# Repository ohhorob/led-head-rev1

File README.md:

# LED Head Unit · Rev 1

## Modular redesign — 2026-11-20

The new modular design lives in separate projects in this same repository:

- [Pico carrier](pico-carrier/README.md): populated control/monitoring schematic and unrouted PCB draft.
- [Power manager](power-manager/README.md): empty KiCad starter project.
- [String daughtercard](string-daughterboard/README.md): existing routed card, preserved.
- [Shared interfaces](shared/README.md): connector pinout, mechanical contract and verification tool.

Open the relevant `.kicad_pro`, rather than opening its PCB on its own. The combined board described below is retained as the earlier design; its control/monitoring circuits have started migrating into the carrier; the power manager remains a starter project.

Open `led-head-rev1.kicad_pro` in KiCad 10. The project contains the schematic, PCB and draft SMT assembly data. The nominal outline is 100 × 73 mm with a notch under the socketed Pico 2 W antenna. The enclosure must leave the antenna end clear of wiring, battery and metal hardware. Check USB and SWD reach, socket height and harness opening clearance against the physical parts.

## Board and harness

| Ref | Connection |
| --- | --- |
| J1 | Shared board-mounted XT60PW-M. Pin 1 is ground and pin 2 is positive. Connect a regulated 5 V supply, a fused 3S LiPo, or a fused 12 V LiFePO₄ camper circuit with BMS protection. Keep the 5 A fuse in the battery harness and size the 5 V source-side fuse for its wiring and load. |
| J3 | High-current panel toggle connections. Board pin 1 (EXT_5V) to S333 lug 3, pin 2 (LED_5V) to lug 2, pin 3 (BUCK_5V) to lug 1. |
| J5 | Toggle auxiliary pole. Board pin 1 to S333 lug 6, pin 2 to lug 5, pin 3 to lug 4. |
| MOD1 | Plug-in Pololu D36V50F5 (4091). Solder two 1×6 female sockets to the carrier and two matching male strips to the module. The pin pitch is 2.54 mm. Use every VIN, VOUT and GND pad. See the mounting details below. |
| J10/J11 | Female 1×20 sockets, on the standard 17.78 mm row spacing. J10 pin 1 is Pico pin 1. J11 pin 1 is Pico pin 21. |
| J12 | NeoTrellis JST-PH. Pins 1–4 on this board are GND, 3.3 V, SDA, SCL. Map the harness wire by wire to the actual keypad; a generic straight-through JST-PH cable is provisional. Check the keypad power budget. |
| J21–J23 | Right-angle JST-XH S3B-XH-A(LF)(SN) string outputs. Pin 1 = GND, pin 2 = DATA, pin 3 = fused and sensed +5 V. Use an XHP-3 housing with SXH-001T-P0.6 contacts and 22 AWG leads to the matching string-side JST-SM connector. Verify the string pin order before crimping. |
| J16 | UART0 for Adafruit 4331. Pin 1 (square, black cable wire) = GND, pin 4 = Pico RX (GP1), pin 5 = Pico TX (GP0). Pins 2, 3 and 6 are unconnected. |
| J17 | SPI0, six-pin JST-PH. Pins 1–6 are GND, switched LED_5V, MISO/GP16, CSn/GP17, SCK/GP18, MOSI/GP19. SPI signals use 3.3 V logic. |
| TP2–TP5 | Standard 2.54 mm 1×2 headers for Logic Pro probes. Pin 1 (square) is signal and pin 2 is ground. TP2 = INA3221 bus SDA, TP3 = INA3221 bus SCL, TP4 = Trellis bus SDA, TP5 = Trellis bus SCL. |

The NKK S333 pole 1 selects the Pololu output or the protected 5 V bypass with OFF between. Label the switch BAT / OFF / 5 V. The second pole grounds buck EN in 5 V mode and grounds the source ID input on the battery setting. Verify switch terminal numbering and lever positions with continuity before marking the enclosure. The switch mounts to the enclosure and connects using a harness. Keep the switch power loop short, use suitably rated wire and strain relief, and ventilate the carrier-mounted Pololu module. The unit and all outputs share DC ground.

The 13.7 kΩ EN pull-down works with the Pololu's nominal internal 100 kΩ pull-up. Nominal loaded cutoff is 9.96 V and restart is 11.20 V from the 1.2/1.35 V EN thresholds. Confirm both with the actual module. The firmware should blank the LEDs before the hardware cutoff. A pack-level threshold cannot identify an imbalanced cell. The camper source uses its own BMS/low-voltage protection. ADC reporting should show volts without inferring chemistry.

Pico GP4/GP5/GP6 remain LED lanes 1–3. GP8/GP9 are hardware I²C0 SDA/SCL for the INA3221, with R7/R8 pull-ups and TP2/TP3 probe headers. NeoTrellis is on hardware I²C1: physical pin 19 (GP14) is SDA and physical pin 20 (GP15) is SCL. The carrier adds no pull-ups to this bus. Use the pull-ups on the connected keypad. GP7 reads the active-low battery-select signal, GP10 reads buck PG, and GP26 is battery ADC. Firmware must add current monitoring, keypad, source sensing and current limiting on top of the existing output paths. The nominal budgets are 1.8 A per string and 4.5 A aggregate LED load on battery. The board power distribution target is 6 A of LEDs plus controller and keypad overhead on external 5 V.

Three TXU0101 buffers replace the originally planned AHCT125. Each output-side supply is taken after its own fuse and shunt, so the data driver isolates when that rail or Pico 3.3 V is absent. Each shunt is 50 mΩ, dropping 100 mV and dissipating 0.20 W at 2 A. Check fuse trip coordination, inrush through the switch and actual connector voltage at full load. Fuse removal and harness changes are performed with power off.

## Four layers, 1 oz copper on both outside layers

Fabrication intent is 1.6 mm FR-4, four layers, **1 oz finished outer copper on both layers**. The 4.8 mm switched trunk, 4.2 mm bypass trunk downstream of the eFuse fan-out, 4.0 mm buck feed, and 1.9 mm per-string top routes are present as copper. String rail fan-outs use 2.3 mm copper and four 0.4 mm drilled vias per string. Positive power routing stays on the outer layers. The dedicated In1 ground plane complements the backside ground pour, with solid connections to high-current through-hole pads. In2 provides room for signal crossovers. Specify 1 oz for the In1 return plane if the fabricator offers it, and verify the chosen stackup on the quote.

IPC-2221 external-trace screening at nominal 35 µm copper gives approximately 3.97 mm for 6.5 A, 2.77 mm for 5 A and 0.78 mm for 2 A at 10 °C rise. Treat these as screening values for straight, uniform traces. Connector annuli, fuse pads, shunt pads, via plating and the minimum width of the actual filled return paths need review as individual bottlenecks. Validate populated electrical and thermal performance with a current-limited bench supply, then at 6 A external and the intended battery load inside the enclosure.

## SMT quote

Request top-side SMT only. Load the supplied BOM and centroid files as quote drafts and review the pin-one and diode orientation on the vendor placement preview. The Pico sockets, screw terminals, XT60 and XH headers, NeoTrellis PH header and bulk electrolytic are through-hole and installed separately. Install the Pololu module and its two headers by hand. The panel switch and mating battery harness are off-board. If using JLCPCB, match the exact manufacturer parts to its catalog before placing the order. In particular, confirm sourcing for the TPS25970ARPWR, the three TXU0101DBVRs, the INA3221, 3 A fuse and shunts. Verify the RPW0010A land pattern, stencil openings, and pin 1 against the assembly preview. PCBWay can quote these by manufacturer part number. Release Gerbers and the placement files together from the same verified PCB revision.

## Review status

KiCad 10 electrical-rule and design-rule reports are included, including board/schematic parity. Both design-rule checks and a vendor placement preview are separate from an electrical prototype test. First articles should verify the physical socket orientation, harness polarity, NeoTrellis pin mapping, S333 auxiliary-contact operation, source-change inrush, 3S cutoff/restart, and voltage drop/temperature in the populated enclosure. Use correctly polarized XT60 leads. The eFuse bypass and input-side status electronics depend on correct polarity.

The firmware is unchanged in its original project. The preserved outputs can drive the existing strings. New sensing, keypad and current-budget behavior require firmware work before relying on the stated limits.

References: [IPC-2221 screening calculator](https://www.digikey.com/en/resources/conversion-calculators/conversion-calculator-pcb-trace-width), [Pico 2 W datasheet](https://datasheets.raspberrypi.com/picow/pico-2-w-datasheet.pdf), [Pololu D36V50F5](https://www.pololu.com/product/4091), [NKK S-series](https://www.nkk.com/pdf/toggle_S.pdf), [TI TXU0101](https://www.ti.com/product/TXU0101), [TI INA3221](https://www.ti.com/product/INA3221), [JLCPCB assembly files](https://jlcpcb.com/help/article/how-to-generate-the-bom-and-centroid-file-from-kicad), [PCBWay assembly files](https://www.pcbway.com/assembly-file-requirements.html).

This revision includes Gerbers and separate plated/non-plated drill files for quote review. The KiCad 10.0.7 checks on the archived revision returned zero ERC violations, zero DRC violations, zero unconnected items and zero schematic-parity issues. The SMT BOM and placement file contain 71 positions. The fabrication and placement files in this package supersede the earlier Rev 1 exports.

## VSYS update

F4 was removed. The switched LED_5V rail now feeds D1 directly via a 0.65 mm branch with a 0.40 mm drill through via. D1 remains in series for USB isolation. Its cathode reaches J11 pad 19 on 0.65 mm front copper. The LED string fuses F1–F3 are retained.

## Connector silkscreen

J12 NEOTRELLIS marks the rotated four-pin JST-PH on the left. The combined string outlets are marked STR 1–3. The D, + and − markings identify data, fused +5 V and ground. J5 identifies the switch logic harness. MOD1 identifies the direct-mount regulator. The shared XT60 input has + and − markings.

## Connector access

The shared J1 XT60 inlet exits the right edge. The three JST-XH string outlets exit the top edge and overhang it for plug access. The J1 mating face projects approximately 5.4 mm beyond the PCB edge. The installed KiCad library has no STEP model for XT60PW-M; use the footprint fabrication outline to review the projection. Verify enclosure openings and wire bend radius with the actual harnesses.

## Pololu mounting

MOD1 uses the Pololu STEP model and generic KiCad models for two 1×6 female sockets and two downward-facing male strips. The modeled stack puts the module PCB underside 11.04 mm above the carrier surface (8.50 mm socket height plus a 2.54 mm male-header spacer). Measure the fully seated hardware before sizing the nylon standoff. The three module mounting-hole centers are indicated on the KiCad Drawings layer for support design. H5 is a 2.2 mm non-plated M2 clearance hole centered at (76.159, 30.759) mm, aligned with the upper-left MOD1 hole in PCB top view.

Viewed from the carrier top with the connector row toward the lower edge of the module, pads 1–6 are on the outer row and pads 7–12 on the inner row. Both rows run left to right.

| Row | Left to right |
| --- | --- |
| Outer (1–6) | VRP, EN, VOUT, VOUT, GND, VIN |
| Inner (7–12) | VRP, PG, VOUT, VOUT, GND, VIN |

Compare the physical module labels to the carrier pin mapping before soldering. Keep airflow around the converter and the existing battery-mode power budget pending a loaded thermal test.

## Shared inlet and status LEDs

| Toggle | Power path | Status |
| --- | --- | --- |
| BAT | J1 through the Pololu | POWER follows the switched rail. FAULT lights if Pololu PG is low after the BAT delay. |
| OFF | Neither throw connects to the switched rail | POWER goes dark as the rail discharges. FAULT is gated off. |
| 5 V | J1 through the TPS25970A eFuse | POWER follows the switched rail. FAULT is gated off. If J1 sees battery voltage, the bypass is blocked. |

The eFuse nominal rising thresholds are 4.33 V for enable and 5.38 V for overvoltage cutoff. With a 768 Ω ILIM resistor the nominal current-limit setpoint is 7.48 A, distinct from the device's 7 A continuous rating. The 6.8 nF DVDT capacitor slows startup when the eFuse enables. Switching to an already energized bypass can still cause inrush into C2. The output uses six plated vias into its 4.2 mm trunk. Inspect the short fan-outs from the RPW power contacts during the loaded test. Validate voltage drop and temperature at the 6 A LED load plus controller overhead before fabrication sign-off.

The red LED uses an input-side 3.3 V LDO independent of Pico power. D2 and D3 isolate the Pico inputs from that supply when the Pico is off. The BAT delay uses a 100 kΩ and 4.7 µF network with a Schmitt input, so timing depends on component and input-threshold tolerances. A depleted battery may be indicated as a fault while input power is sufficient to light the LED. If J1 is unplugged, the indicator has no supply.

With a current-limited bench source and the strings disconnected, test each switch mode, verify the overvoltage cutoff with battery-level input in 5 V mode, and scope the switched rail during hot-plug and source changes. Verify the fault LED with PG low while the Pico supply is absent. Follow with the loaded thermal and enclosure tests.

[TI TPS2597 datasheet](https://www.ti.com/lit/ds/symlink/tps2597.pdf) · [TI SN74LVC1G57 datasheet](https://www.ti.com/lit/ds/symlink/sn74lvc1g57.pdf)

## Pre-fabrication board review

Use Panasonic EEU-FR1C102 for C2 (1,000 µF, 16 V, 10 mm body and 5 mm lead pitch). The suffixed EEU-FR1C102L uses 3.5 mm lead pitch. The U4 INA3221 and R11–R13 shunt land patterns are in the project footprint library and follow the TI and Vishay reference dimensions. The SMT placement file was exported from the manually routed board. The native KiCad PCB is the source for subsequent edits.

The current layout passed KiCad ERC, DRC and schematic parity. The documented design-rule exclusions remain in the reports. Review the silkscreen and regenerate all final fabrication outputs from the resulting PCB. Verify assembly sourcing and rotation against the vendor preview before ordering.

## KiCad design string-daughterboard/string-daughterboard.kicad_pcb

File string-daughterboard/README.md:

# String daughterboard

Open `string-daughterboard.kicad_pro` in KiCad Project Manager. This is the existing manually routed daughtercard in the same repository as the carrier and power-manager projects.

One string channel has:

- F1: Littelfuse 0451003.MRL, 3 A fuse.
- **R1: Vishay WSL2512R0250FEA, 25 mOhm, 1%, 1 W, 2512.**
- U1: TXU0101 data translator, followed by R2, 220 ohm.
- J2: right-angle JST-XH output; pin 1 GND, pin 2 DATA, pin 3 string +5 V.
- D1: Würth 1312020030000 (2 × 2 mm) status pixel on fused 5 V before the shunt (SHUNT_HI).
- C1/C2: 100 nF bypass capacitors for the TXU0101 supplies. C3 is a dedicated 100 nF bypass for D1 on the back of the card.

The new shunt value replaces 50 mOhm. At 2 A it drops 50 mV and dissipates 0.10 W. The carrier uses two PAC1934 monitors; the 100 mV sense range corresponds to nominal 4 A full scale with this resistor. Firmware must use 0.025 ohm. The 3 A fuse is not a precise 2 A current limiter.

The R1 footprint now has the value-neutral name `StringCard:Vishay_WSL2512`. Its pad geometry is unchanged. The older `_50mR` library item is retained only as a legacy definition; the current schematic and board use the value-neutral item. No track, via, zone, outline, component position or pad geometry changed during the shunt update.

## Card interface and mechanics

J1 is the PCB edge itself, mating with a carrier-mounted Sullins EBC06DRAS. Do not fit a socket on this daughtercard. Nominal board thickness is 1.6 mm, with six contacts per face at 2.54 mm pitch. The present board is 22 × 26.5 mm overall, including its 17.4 mm wide × 8 mm tongue. Printed rails provide retention; there are no mounting holes on this daughtercard. Check physical mating and card-facing direction with the socket before fabrication.

| Finger | Net | Purpose |
| --- | --- | --- |
| A1, B1 | GND | Parallel power returns |
| A2, B2 | IN_5V | Parallel regulated 5 V input contacts, 2 A nominal total |
| A3 | PERIPH_3V3 | String translator input-side supply |
| B3 | STRING_DATA_IN | 3.3 V string data |
| A4 | SHUNT_HI | Kelvin sense upstream of the shunt, after fuse |
| B4 | STRING_5V | Kelvin sense downstream of shunt |
| A5 | STATUS_DATA_IN | 5 V logic status pixel input |
| B5 | STATUS_DATA_OUT | Regenerated status output to next slot |
| A6, B6 | Unconnected | Reserved |

A is front copper and B is back copper. Looking at the front with the insertion tip at the bottom, positions 1–6 run left to right. The carrier socket orientation is documented separately; this front-view convention must not be confused with the socket's component-side solder-tail view.

The Kelvin pair carries measurement signals, not load current. The status pixel draws from the fused 5 V node upstream of R1, so its current does not flow through the string shunt. The carrier translates GP20 to 5 V before slot 1. Use this card revision throughout the chain. Use the specified Würth 1312020030000 part; avoid driving an unpowered card. Swaps are power-off only. Enclosure guides must prevent reversed insertion.

## Validation and exports

After the shunt update: zero ERC violations, zero DRC violations, zero unrouted connections and zero schematic-parity issues. The shared checker verifies the edge pinout, card geometry, carrier monitoring connections and R1's selected value/part number.

Existing manufacturing folders are historical snapshots and were not regenerated. The shunt change does not change fabrication copper, but their embedded board metadata or assembly references may still say 50 mOhm. Use the current native design and **WSL2512R0250FEA** for new component purchases.

Do not rerun the archived creation scripts over the routed board. Schematic UUIDs and PCB footprint paths must remain linked so F8 updates the same components.

See [shared interface contract](../shared/README.md), [footprint audit](footprint-audit.md), and [carrier project](../pico-carrier/README.md).

## Status LED update — 2026-11-23

Restore point before this change: `3f7ae29`. D1 now uses Würth 1312020030000, with the manufacturer's rev26a footprint and matching STEP model. Library geometry is unchanged from Würth; its model path is project-relative. Symbol numbering is remapped while retaining existing schematic wires: 1 DOUT, 2 VDD (PERIPH_3V3), 3 DIN, 4 GND. The original D1 PCB position, rotation, UUID and schematic path are retained. All other footprints, traces, vias and outline geometry are unchanged. Copper zones were refilled.

ERC passes; the board/library footprint and schematic pin mapping were verified. The original layout passed DRC before replacement; the smaller D1 pads require local rerouting. Current DRC reports shorts from existing STATUS_DATA_IN tracks to D1 supply/ground pads, supply-via clearance, dangling old DIN/DOUT tracks, and an incomplete D1 ground thermal. Reconnect all four D1 pins before fabrication. C1/C2 remain 100 nF in their existing positions; place the LED bypass close to the new supply/ground pads when rerouting. Manufacturing exports are historical and must not be used for this changed layout.

Carrier assembly STEP snapshots have been refreshed to show the smaller LED. No carrier layout file changed. The shared interface checker currently flags pre-existing carrier GPIO and monitor-channel permutations against its older JSON contract; schematic and PCB agree with one another at those endpoints. These mappings were not changed here.

Source: https://www.we-online.com/en/components/products/WL-ICLED — KiCad_WL-ICLED (rev26a).zip. Würth CAD license and attribution are retained in `Wurth-CAD-LICENSE.txt`. D1's manufacturer STEP is under `../models/U_Wurth_WL-ICLED_1312020030000.step`.

## Status chain at 5 V — 2026-11-24

D1 retains the Würth 1312020030000 and its footprint. D1 VDD now connects to SHUNT_HI, with C3 providing local bypass. The interface pin assignments are unchanged. Use the matching carrier revision with U6 and generate fresh fabrication files for this routed revision.

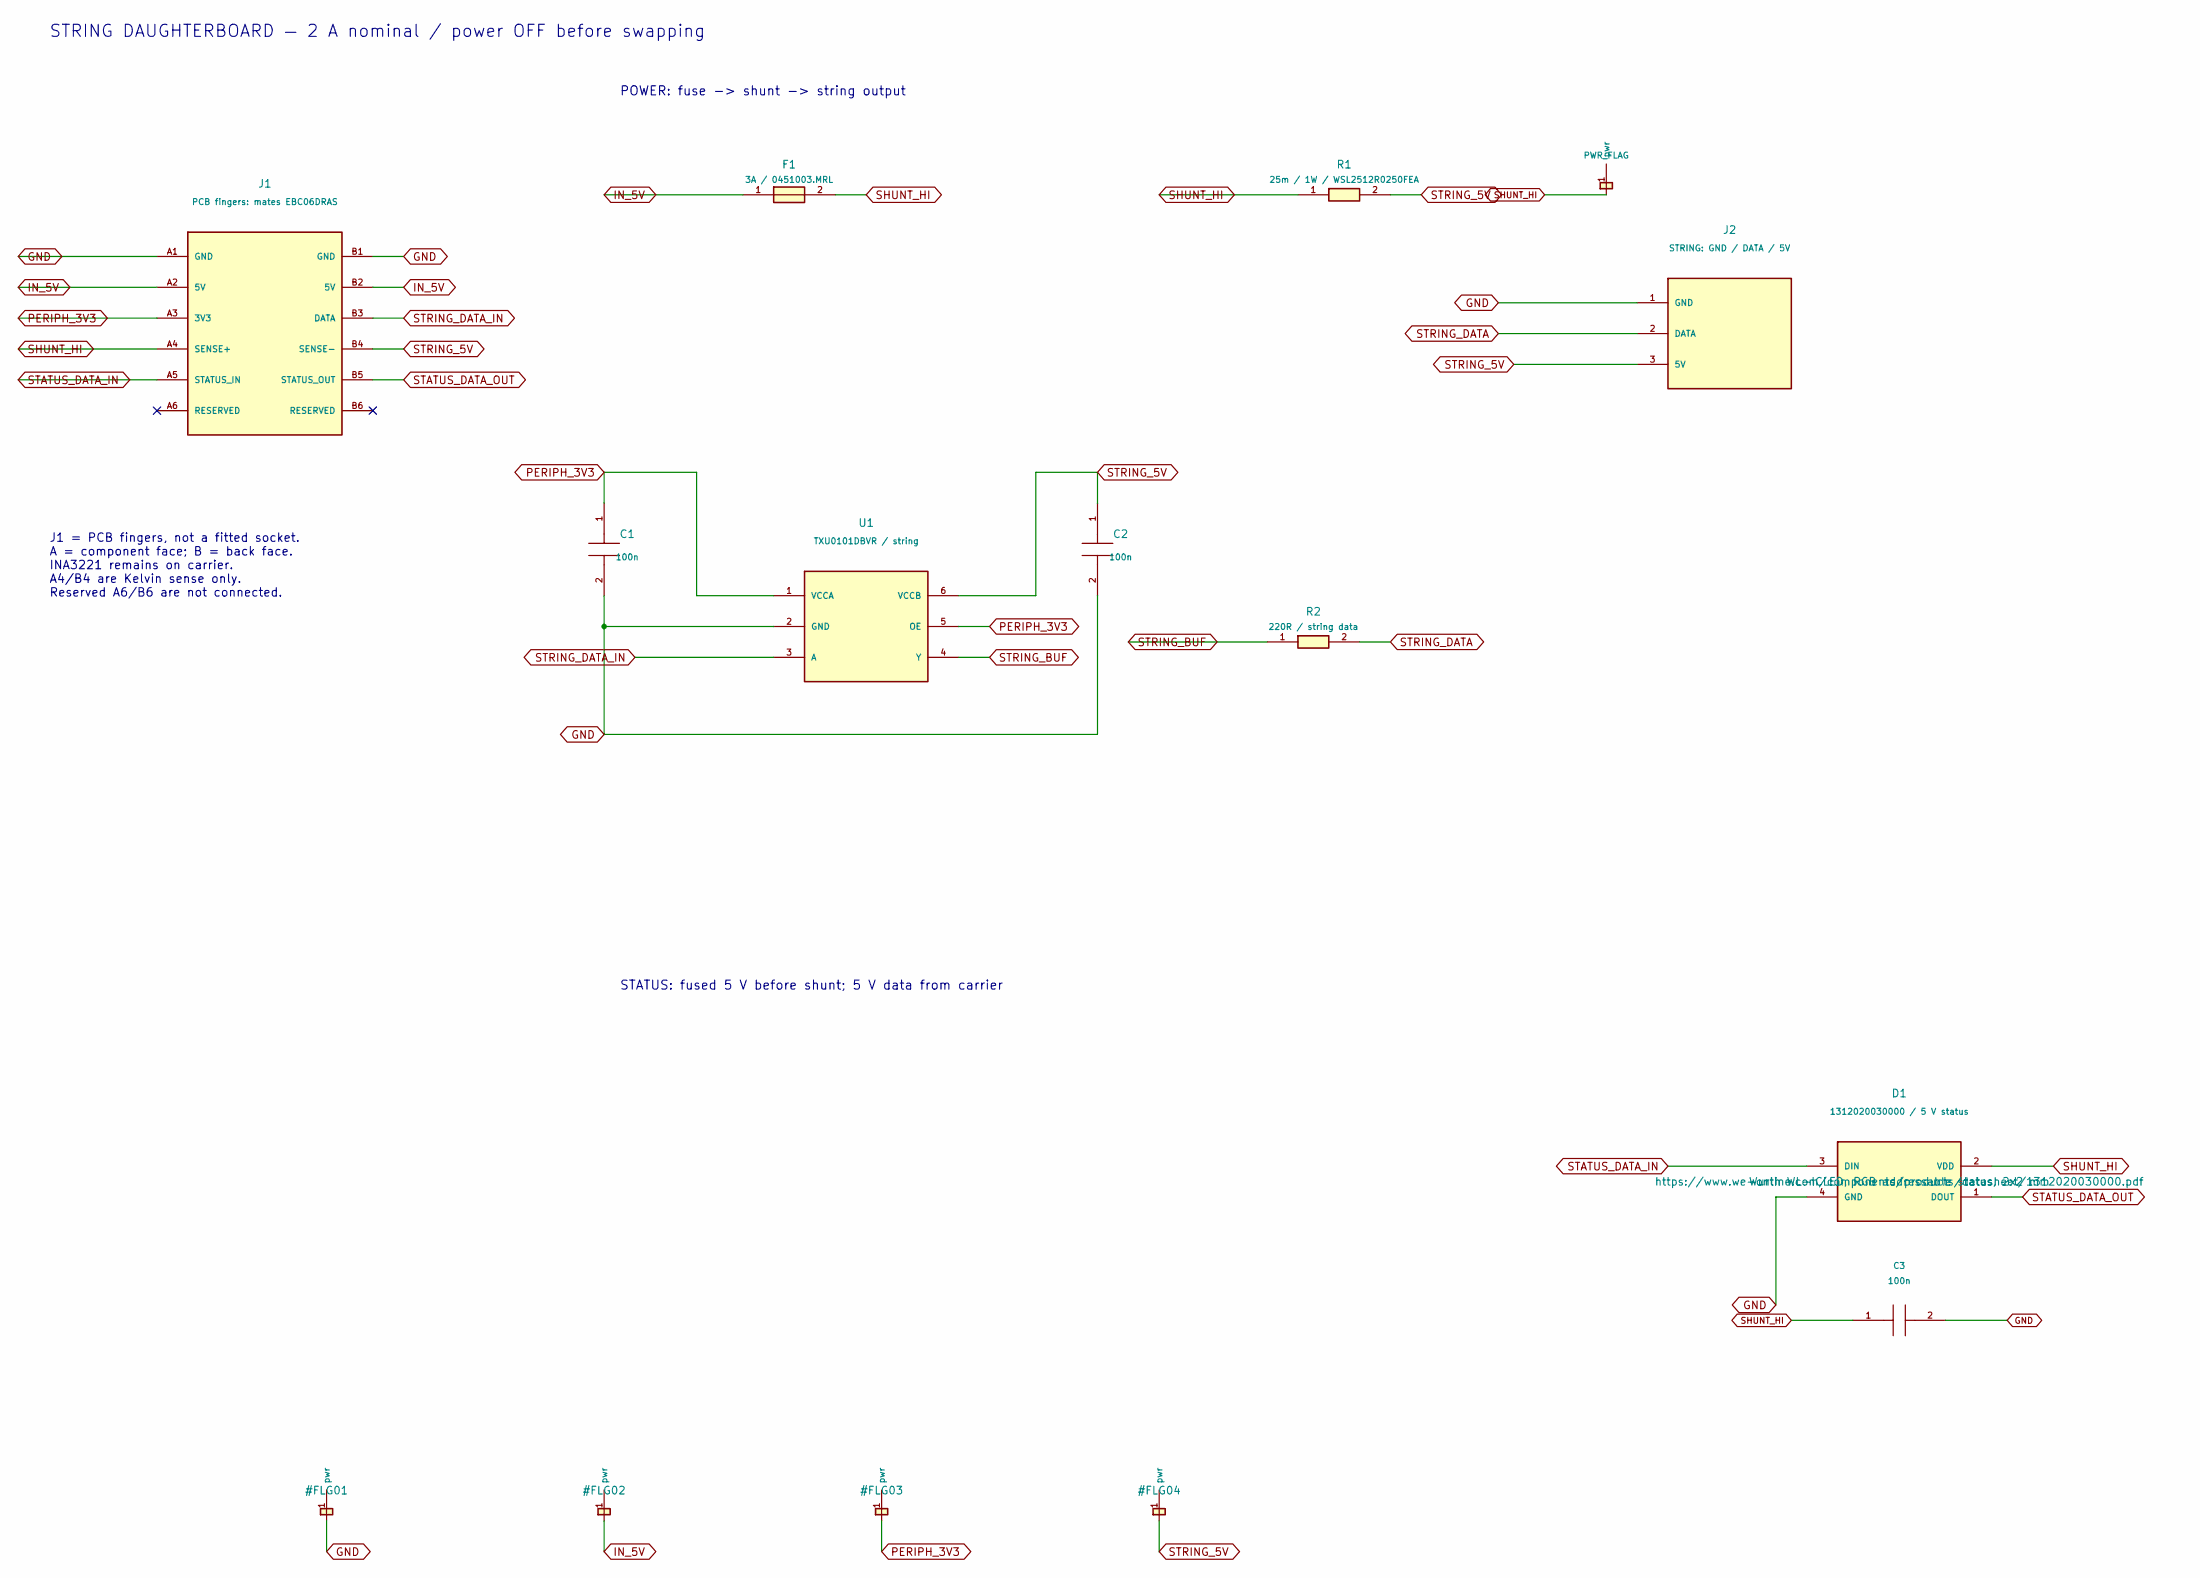
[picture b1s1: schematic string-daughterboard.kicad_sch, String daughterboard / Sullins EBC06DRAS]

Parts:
C1, C2: 100n; C_0805_2012Metric_Pad1.18x1.45mm_HandSolder
C3: 100n; C_0603_1608Metric
D1: 1312020030000 / 5 V status; U_Wurth_WL-ICLED_1312020030000; MPN 1312020030000; DigiKey Part Number 732-1312020030000CT-ND
F1: 3A / 0451003.MRL; Fuse_Littelfuse-NANO2-451_453
J1: PCB fingers: mates EBC06DRAS; Sullins_EBC06DRAS_Mating_Card_2x06_P2.54mm
J2: STRING: GND / DATA / 5V; JST_XH_S3B-XH-A_1x03_P2.50mm_Horizontal
R1: 25m / 1W / WSL2512R0250FEA; Vishay_WSL2512; MPN WSL2512R0250FEA
R2: 220R / string data; R_0805_2012Metric_Pad1.20x1.40mm_HandSolder
U1: TXU0101DBVR / string; SOT-23-6_Handsoldering

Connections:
GND: C1.2, C2.2, C3.2, D1.4 (GND), J1.A1 (GND), J1.B1 (GND), J2.1 (GND), U1.2 (GND)
IN_5V: F1.1, J1.A2 (5V), J1.B2 (5V)
PERIPH_3V3: C1.1, J1.A3 (3V3), U1.1 (VCCA), U1.5 (OE)
SHUNT_HI: C3.1, D1.2 (VDD), F1.2, J1.A4 (SENSE+), R1.1
STATUS_DATA_IN: D1.3 (DIN), J1.A5 (STATUS_IN)
STATUS_DATA_OUT: D1.1 (DOUT), J1.B5 (STATUS_OUT)
STRING_5V: C2.1, J1.B4 (SENSE-), J2.3 (5V), R1.2, U1.6 (VCCB)
STRING_BUF: R2.1, U1.4 (Y)
STRING_DATA: J2.2 (DATA), R2.2
STRING_DATA_IN: J1.B3 (DATA), U1.3 (A)

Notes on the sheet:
J1 = PCB fingers, not a fitted socket. A = component face; B = back face. INA3221 remains on carrier. A4/B4 are Kelvin sense only. Reserved A6/B6 are not connected.
POWER: fuse -> shunt -> string output
STRING DAUGHTERBOARD — 2 A nominal / power OFF before swapping
STATUS: fused 5 V before shunt; 5 V data from carrier

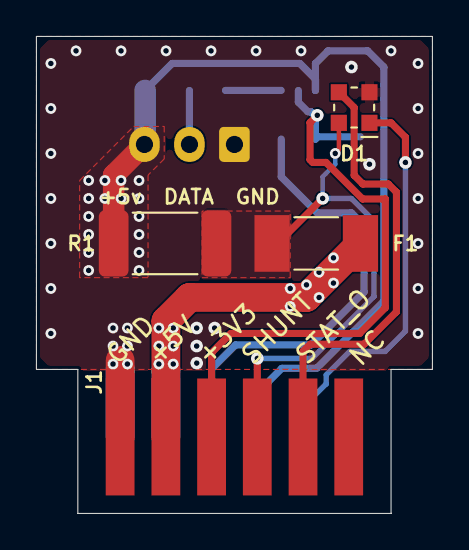
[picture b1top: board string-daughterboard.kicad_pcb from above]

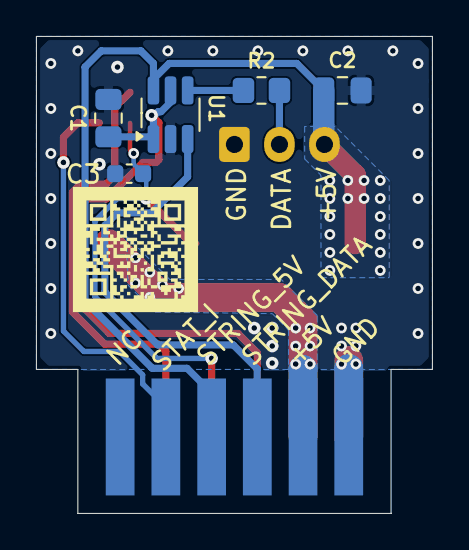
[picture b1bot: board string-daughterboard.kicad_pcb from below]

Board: 2 copper layers, 22.0 x 26.5 mm, 11 parts (6 on the bottom side), 10 nets.

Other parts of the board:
QR1: QR_GitHub_led-head-rev1_7mm

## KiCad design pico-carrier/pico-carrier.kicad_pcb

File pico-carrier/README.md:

# Pico 2 W carrier

Open `pico-carrier.kicad_pro` through KiCad Project Manager. This is a populated schematic and an **unrouted placement draft**, not a fabrication release. No board outline is assigned yet.

The root schematic links two sheets:

- `control.kicad_sch`: Pico sockets, UART0, SPI0, two I2C buses and probe headers, ADC breakout, SWD header and J-Link connector.
- `string-slots.kicad_sch`: eight vertical Sullins EBC06DCWN sockets.
- `current-monitoring.kicad_sch`: two PAC1934 monitors, bypass capacitors wired directly to VDD/VDD_IO, and source/PG pull-ups.

String data for slots 1–8 uses GP4, GP5, GP6, GP2, GP3, GP11, GP12 and GP13 respectively. GP20 drives U6 (TXU0101DBVR), which translates the head of the eight-pixel status chain to 5 V before J21 A5. The last pixel's output is intentionally unused. The PAC1934 monitor bus uses GP8/GP9 on I2C0, with pull-ups to the external peripheral 3.3 V rail. NeoTrellis uses GP14/GP15 on I2C1, with no added pull-ups. Its connector pin 2 now supplies **5 V VIN**, rather than the Pico's 3.3 V output. Wire the harness to the tile's VIN input and retain 3.3 V I2C pull-ups.

`PICO_3V3` is the Pico regulator output and debugger reference. `PERIPH_3V3` is the separate regulator's output; they are distinct nets. The Pico's VSYS is supplied through the existing SS14 isolation diode from `IN_5V`. `PICO_PG`, `PICO_BATT_SEL_N` and the battery ADC path await the power-manager interface; their protective scaling/voltage behavior is not complete here.

The PCB contains 34 footprints with schematic UUID paths and matching nets. Positions are initial organization only. Existing Pico socket geometry and its original project 3D model were retained; validate that model against the exact Pico hardware before using it for enclosure clearance. No tracks or fill zones were copied from the old combined board.

U4 and U5 are PAC1934T-I/JQ, 4 × 4 mm UQFN with 0.65 mm pitch. U4 ADDRSEL is grounded (0x10); U5 ADDRSEL is tied to VDD (0x1F). Both VDD and VDD_IO have separate 100 nF bypasses, physically grouped near the IC on the draft PCB. SLOW is pulled low through 10k and PWRDN is held high. The standard KiCad land pattern was checked against Microchip C04-2257A: 0.80 × 0.35 mm outer pads, 4.00 mm opposed-pad-centre spacing, 0.65 mm pitch and a 2.7 mm centre pad, without thermal vias.

## Socket footprint

J21–J28 use the vertical **Sullins EBC06DCWN**. The footprint has 12 plated contacts, a 2.54 mm column pitch, 5.08 mm between rows, 1.10 mm finished drills, and 1.70 × 2.20 mm pads. The no-ear housing measures 21.84 × 9.40 mm and sits 15.49 mm above the board. The printed card rails provide retention and must prevent reversed insertion. Test-fit a socket and a daughtercard to confirm contact orientation and clearance.

See the [Sullins C11424 Rev D drawing](../shared/reference/Sullins_C11424_RevD_CW_CT.pdf) and [footprint verification notes](../models/Sullins_EBC06DCWN_model-notes.md).

## Checks and remaining work

KiCad CLI reports zero ERC violations and zero schematic-parity issues. The interface checker passes for all eight sockets and both monitors and the unchanged daughtercard. The draft has 159 unrouted connections and no board outline; DRC correctly reports these unfinished items. No checks were disabled to hide them.

Choose the power interconnect using [power connection options](power-connection-options.md), then establish board size, stack height, card-facing direction and rail locations. Review USB/SWD/cable access before routing. Keep both supply rails and their power-up/down behavior in the electrical review.

## Firmware configuration

Use 0.025 ohm for every daughtercard shunt. PAC1934 unipolar shunt-voltage scaling gives a nominal 4 A full-scale range; the nominal 2 A load produces 50 mV and 0.10 W at the shunt. Keep the 3 A fuse; measurement range does not set a current limit. Apply the low-sample-rate REFRESH workaround from Microchip errata DS80001160A.

Unlike the INA3221 connection previously used, the PAC1934 measures bus voltage at SENSE+, upstream of the shunt. For delivered string voltage use `Vload = Vbus - Vshunt`; for delivered power use `I * Vload`. Its reported input-side power includes shunt dissipation. No firmware driver has been implemented by this hardware change.

For all eight strings at 2 A, provision 16 A plus controller/peripheral overhead. The previously proposed four-contact Mini-Fit harness was discussed for the smaller system; its final circuit count/wire size and the converter budget must be reviewed for this expanded carrier before routing the main feed.

## Power-board input

J19 is a **10-position Molex Mini-Fit Jr**, PCB header **0039281103**, footprint `Connector_Molex:Molex_Mini-Fit_Jr_5566-10A_2x05_P4.20mm_Vertical`. It combines the regulated string rail and peripheral rail in one harness. Mating housing: **0039012100**; female contacts: **0039000039**, selected for 18–24 AWG. The intended main power conductors are 18 AWG; check the complete connector/wire derating and loaded temperature before release.

| Pins | Net |
| --- | --- |
| 1–4 | IN_5V, parallel regulated 5 V conductors |
| 5 | PERIPH_3V3, separate peripheral regulator output |
| 6–10 | GND, parallel returns |

PERIPH_3V3 remains separate from Pico 3V3(OUT). The carrier connector is placed to the right of the present layout and marked POWER IN; the user can position it. Existing parts and routing were preserved. The briefly added two-pin JST input was removed, including its symbol, footprint and labels.

The matching power-manager circuitry/connector still needs implementation. This connector does not carry source-ID, PG or divided battery ADC signals; their inter-board connection remains to be designed. No 16 A harness rating is inferred merely by multiplying the catalogue single-contact rating.

## Dedicated 5 V module — 2026-11-21

The power-manager project is now the simple dedicated-5-V module: one XT60, the WEBENCH TPS62091 3.3 V converter and Mini-Fit output J5. Connect it to carrier J19 with the existing straight-through ten-pin power cable. The carrier pinout is unchanged: 1–4 IN_5V, 5 PERIPH_3V3, 6–10 GND.

Carrier J20 remains a reserved five-pin telemetry connector for a future separate battery module: 1 GND, 2 PICO_3V3, 3 BAT_ADC, 4 PICO_PG, 5 PICO_BATT_SEL_N. It is parked outside the outline at (110,135) mm. It has no matching connector on the dedicated 5 V module and is not needed for that module to supply power. The future battery-module interface is deferred.

The shared power interface checker verifies the implemented main cable and the reserved carrier-side telemetry pinout separately. No carrier layout or routing was changed while replacing the combined power-manager design with the dedicated-supply module.

## Status chain at 5 V — 2026-11-24

U6 sits on front copper near the Pico socket, with C44 on VCCA (PICO_3V3) and C45 on VCCB (IN_5V). OE is tied to PICO_3V3. The 5 V output STATUS_RGB_5V goes to slot 1 (J21 A5). The existing inter-slot status links are unchanged. Use the matching daughterboard revision with D1 powered from fused 5 V before its shunt. A6 and B6 remain reserved.

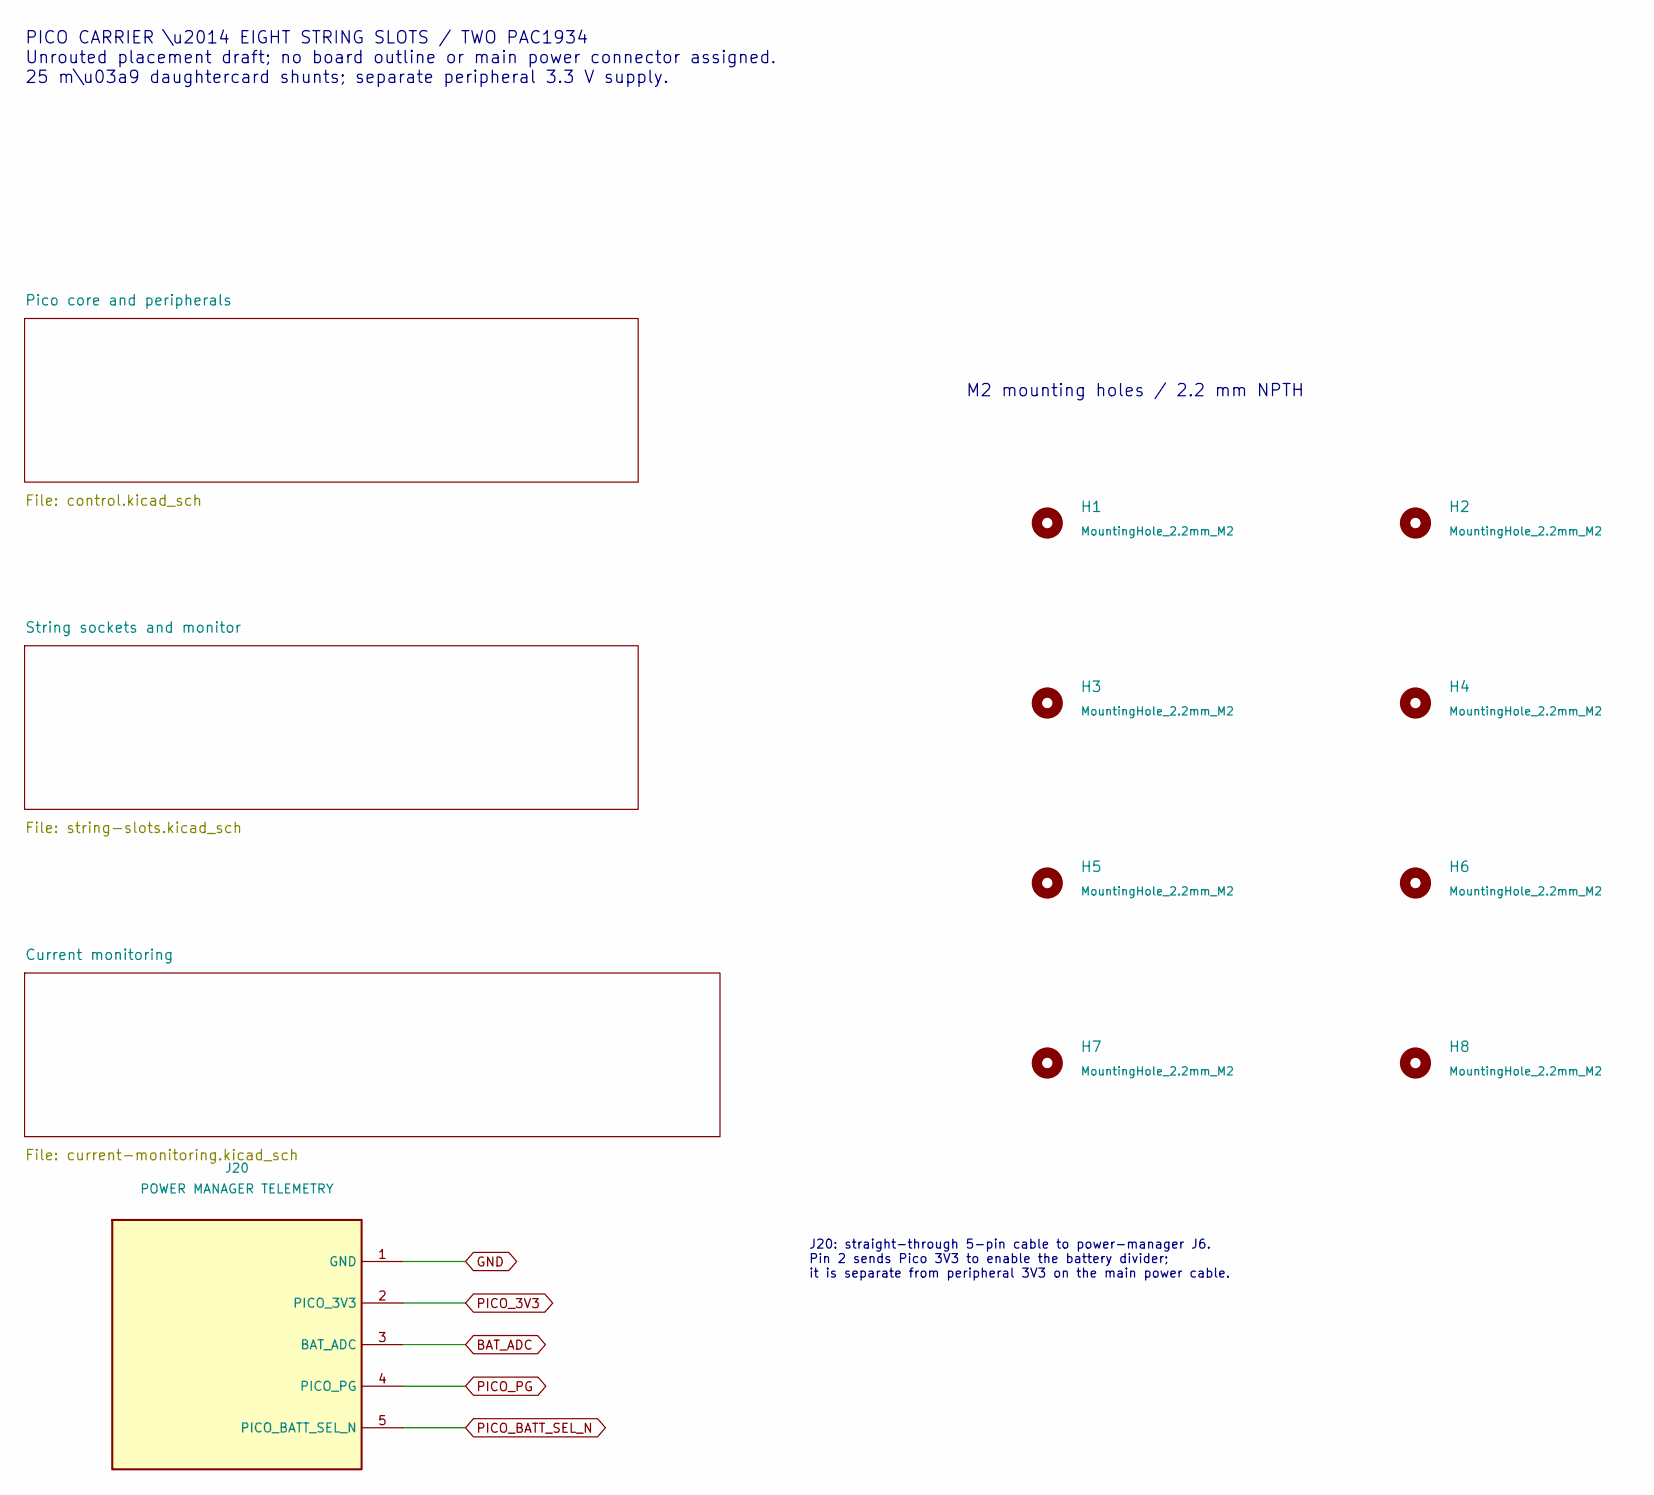
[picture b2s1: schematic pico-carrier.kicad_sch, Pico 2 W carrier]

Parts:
H1, H2, H3, H4, H5, H6, H7, H8: MountingHole_2.2mm_M2
J20: POWER MANAGER TELEMETRY; JST_XH_B5B-XH-A_1x05_P2.50mm_Vertical; MPN B5B-XH-A(LF)(SN)

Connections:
BAT_ADC: J20.3 (BAT_ADC); also elsewhere on the board
GND: J20.1 (GND); also elsewhere on the board
PICO_3V3: J20.2 (PICO_3V3); also elsewhere on the board
PICO_BATT_SEL_N: J20.5 (PICO_BATT_SEL_N); also elsewhere on the board
PICO_PG: J20.4 (PICO_PG); also elsewhere on the board

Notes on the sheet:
PICO CARRIER \u2014 EIGHT STRING SLOTS / TWO PAC1934 Unrouted placement draft; no board outline or main power connector assigned. 25 m\u03a9 daughtercard shunts; separate peripheral 3.3 V supply.
M2 mounting holes / 2.2 mm NPTH
J20: straight-through 5-pin cable to power-manager J6. Pin 2 sends Pico 3V3 to enable the battery divider; it is separate from peripheral 3V3 on the main power cable.

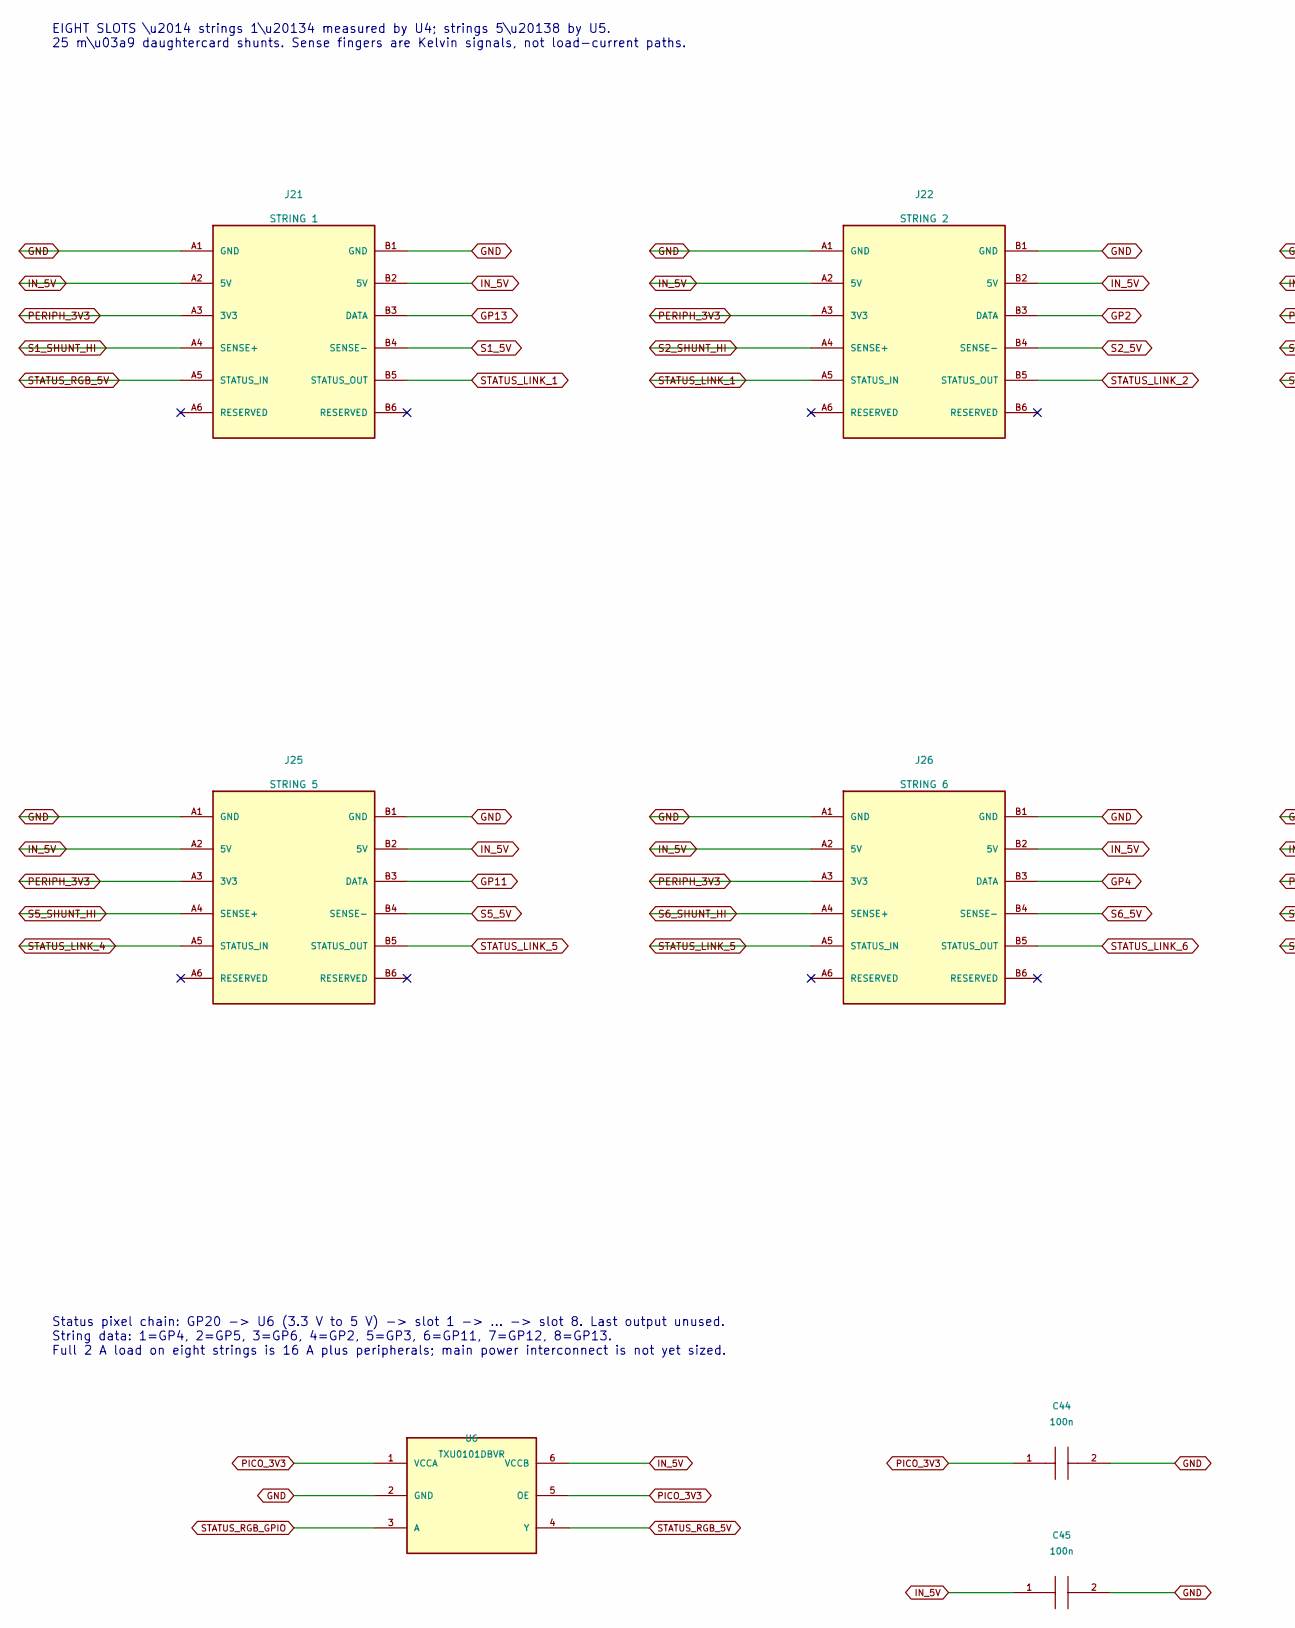
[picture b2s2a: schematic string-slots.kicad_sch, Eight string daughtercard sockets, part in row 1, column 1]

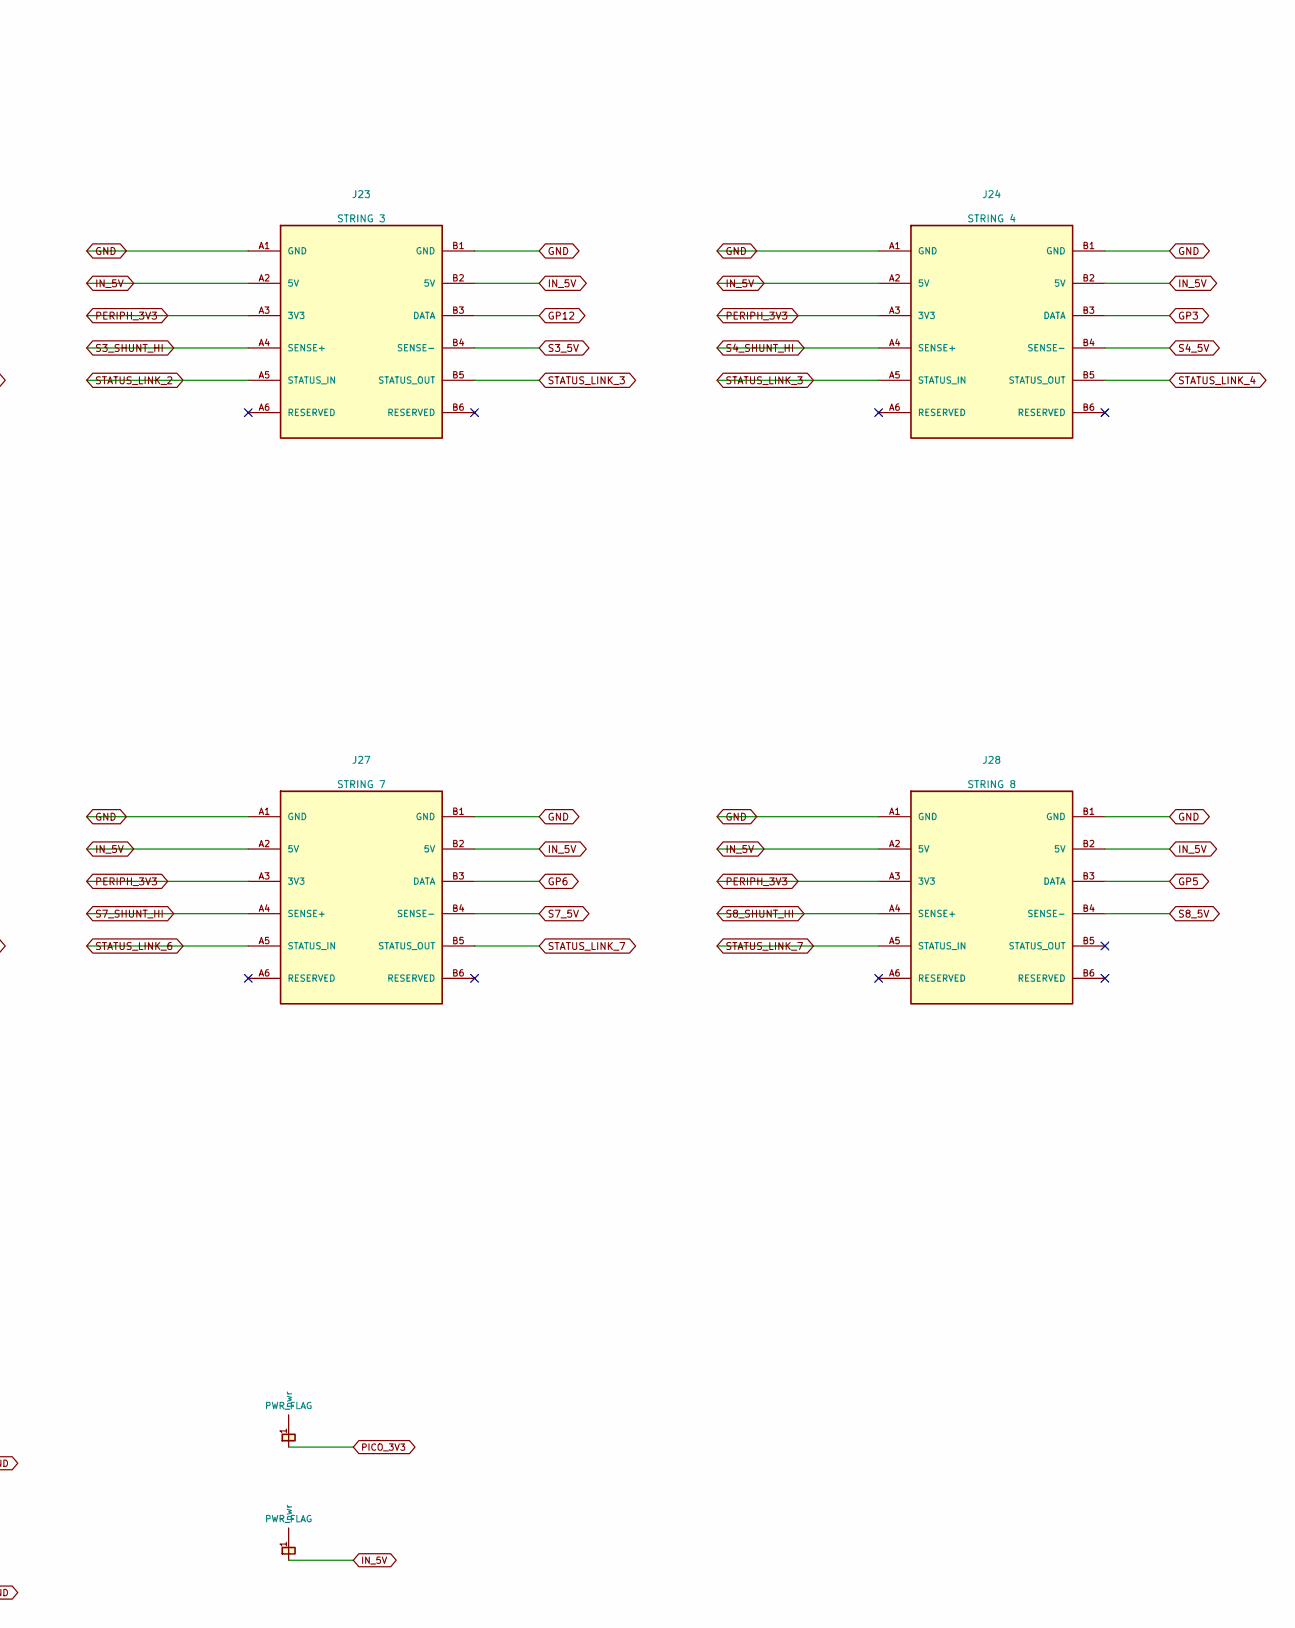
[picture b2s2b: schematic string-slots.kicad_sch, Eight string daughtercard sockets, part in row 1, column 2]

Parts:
C44, C45: 100n; C_0805_2012Metric_Pad1.18x1.45mm_HandSolder
J21: STRING 1; Sullins_EBC06DCWN_Socket_2x06_P2.54mm_Vertical
J22: STRING 2; Sullins_EBC06DCWN_Socket_2x06_P2.54mm_Vertical
J23: STRING 3; Sullins_EBC06DCWN_Socket_2x06_P2.54mm_Vertical
J24: STRING 4; Sullins_EBC06DCWN_Socket_2x06_P2.54mm_Vertical
J25: STRING 5; Sullins_EBC06DCWN_Socket_2x06_P2.54mm_Vertical
J26: STRING 6; Sullins_EBC06DCWN_Socket_2x06_P2.54mm_Vertical
J27: STRING 7; Sullins_EBC06DCWN_Socket_2x06_P2.54mm_Vertical
J28: STRING 8; Sullins_EBC06DCWN_Socket_2x06_P2.54mm_Vertical
U6: TXU0101DBVR; SOT-23-6_Handsoldering; MPN TXU0101DBVR

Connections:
GND: C44.2, C45.2, J21.A1 (GND), J21.B1 (GND), J22.A1 (GND), J22.B1 (GND), J23.A1 (GND), J23.B1 (GND), J24.A1 (GND), J24.B1 (GND), J25.A1 (GND), J25.B1 (GND), J26.A1 (GND), J26.B1 (GND), J27.A1 (GND), J27.B1 (GND), J28.A1 (GND), J28.B1 (GND), U6.2 (GND); also elsewhere on the board
GP2: J22.B3 (DATA); also elsewhere on the board
GP3: J24.B3 (DATA); also elsewhere on the board
GP4: J26.B3 (DATA); also elsewhere on the board
GP5: J28.B3 (DATA); also elsewhere on the board
GP6: J27.B3 (DATA); also elsewhere on the board
GP11: J25.B3 (DATA); also elsewhere on the board
GP12: J23.B3 (DATA); also elsewhere on the board
GP13: J21.B3 (DATA); also elsewhere on the board
IN_5V: C45.1, J21.A2 (5V), J21.B2 (5V), J22.A2 (5V), J22.B2 (5V), J23.A2 (5V), J23.B2 (5V), J24.A2 (5V), J24.B2 (5V), J25.A2 (5V), J25.B2 (5V), J26.A2 (5V), J26.B2 (5V), J27.A2 (5V), J27.B2 (5V), J28.A2 (5V), J28.B2 (5V), U6.6 (VCCB); also elsewhere on the board
PERIPH_3V3: J21.A3 (3V3), J22.A3 (3V3), J23.A3 (3V3), J24.A3 (3V3), J25.A3 (3V3), J26.A3 (3V3), J27.A3 (3V3), J28.A3 (3V3); also elsewhere on the board
PICO_3V3: C44.1, U6.1 (VCCA), U6.5 (OE); also elsewhere on the board
S1_5V: J21.B4 (SENSE-); also elsewhere on the board
S1_SHUNT_HI: J21.A4 (SENSE+); also elsewhere on the board
S2_5V: J22.B4 (SENSE-); also elsewhere on the board
S2_SHUNT_HI: J22.A4 (SENSE+); also elsewhere on the board
S3_5V: J23.B4 (SENSE-); also elsewhere on the board
S3_SHUNT_HI: J23.A4 (SENSE+); also elsewhere on the board
S4_5V: J24.B4 (SENSE-); also elsewhere on the board
S4_SHUNT_HI: J24.A4 (SENSE+); also elsewhere on the board
S5_5V: J25.B4 (SENSE-); also elsewhere on the board
S5_SHUNT_HI: J25.A4 (SENSE+); also elsewhere on the board
S6_5V: J26.B4 (SENSE-); also elsewhere on the board
S6_SHUNT_HI: J26.A4 (SENSE+); also elsewhere on the board
S7_5V: J27.B4 (SENSE-); also elsewhere on the board
S7_SHUNT_HI: J27.A4 (SENSE+); also elsewhere on the board
S8_5V: J28.B4 (SENSE-); also elsewhere on the board
S8_SHUNT_HI: J28.A4 (SENSE+); also elsewhere on the board
STATUS_LINK_1: J21.B5 (STATUS_OUT), J22.A5 (STATUS_IN)
STATUS_LINK_2: J22.B5 (STATUS_OUT), J23.A5 (STATUS_IN)
STATUS_LINK_3: J23.B5 (STATUS_OUT), J24.A5 (STATUS_IN)
STATUS_LINK_4: J24.B5 (STATUS_OUT), J25.A5 (STATUS_IN)
STATUS_LINK_5: J25.B5 (STATUS_OUT), J26.A5 (STATUS_IN)
STATUS_LINK_6: J26.B5 (STATUS_OUT), J27.A5 (STATUS_IN)
STATUS_LINK_7: J27.B5 (STATUS_OUT), J28.A5 (STATUS_IN)
STATUS_RGB_5V: J21.A5 (STATUS_IN), U6.4 (Y)
STATUS_RGB_GPIO: U6.3 (A); also elsewhere on the board

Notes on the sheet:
Status pixel chain: GP20 -> U6 (3.3 V to 5 V) -> slot 1 -> ... -> slot 8. Last output unused. String data: 1=GP4, 2=GP5, 3=GP6, 4=GP2, 5=GP3, 6=GP11, 7=GP12, 8=GP13. Full 2 A load on eight strings is 16 A plus peripherals; main power interconnect is not yet sized.
EIGHT SLOTS \u2014 strings 1\u20134 measured by U4; strings 5\u20138 by U5. 25 m\u03a9 daughtercard shunts. Sense fingers are Kelvin signals, not load-current paths.
